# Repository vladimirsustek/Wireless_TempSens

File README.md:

<h2>The BleuPill tempSens!</h2>

<h2>Intended usages</h2>
<ol>
  <li>Battery operating low-power temperature sensor</li>
  <li>PID controlled loop (PWM H-Bridge)</li>
</ol>

System consist of: <br> 
<ol>
  <li>Core MCU - STM32F103C8T6 BluePill module</li>
  <li>nRF24L01+ wireless module</li>
  <li>LM75AD temperature sensor</li>
  <li>2x NTC 10k on-board sensor</li>
  <li>Optional PWM H-Bridge DRV8220</li>
  <li>Optional self-measuring current consumption circuit (OA LMV358 1/2 sensing 10Ohm) - curr</li>
  <li>Optional OA channel sensing general purpose external voltage (LMV358 2/2) - oagp</li>
</ol>

This project has default structure for STM's [STM32CudeIDE](https://www.st.com/en/development-tools/stm32cubeide.html#:~:text=STM32CubeIDE%20is%20an%20advanced%20C,and%20GDB%20for%20the%20debugging.)
.Download this free IDE to build the project.<br/>
**The project utilizes default STM's HAL drivers**<br/>

To see complete PCB design, see "PCB_design" directory, or at least the [schematic](/PCB_design/Wireless_TempSens.pdf)

<h2>Battery operating low-power temperature sensor</h2>

System shall periodically send all measured data in specified interval.<br/>
System shall consume minimal power when not measuring or sending the data .<br/>
System shall be parametrized over the UART (115200b, LF terminated):
<ol>
  <li>nRF24L01+'s TX_ADR: 5 - bytes e.g. ADR01</li>
  <li>nRF24L01+'s RX_ADR_P0: 5 - bytes e.g. ADR01</li>
  <li>PERIOD INTERVAL: number 0 - 255 representing low power mode in seconds</li>
</ol>
Note that the UART connection is meant as optional for parametrization and logging.

<h3>BluePill modifications</h3>
Due to the permanetly on PWR LED (when connected to the 3V3)<br/>
and the PC13 LED (on due to the TAMPER RTC-ALARM PIN),<br/>
their pull-up resistors has been desoldered (R5, R1).<br/>
Note that each LED consumed cca 2mA what is inadmissible for low power mode.

<h3>Startup and operational sequence<br/></h3>
After reset, the application sends UART messages:<br/><br/>
<em>LISTENING FOR PARAMETRIZATION 10000 ms<br/>
FORMAT: ADR01 ADR01 010</em><br/>...displaying currently set parameters<br/><br/>
When a new parameters has been received and set, they are displayed:<br/><br/>
<em>TX_ADR ADR01<br/>
RX_ADR ADR01<br/>
STOP_PERIOD 58<br/>
NORMAL MODE STARTED</em><br/>
When no or invalid parameters were provided:<br/><br/>
<em>NO CHANGES APPLIED<br/>
NORMAL MODE STARTED</em/>

Then, once per pre-set interval the system sends over the UART message:<br/><br/>
<em>TMPE 23750 - the temperature by the LM75AD [m°C]<br/>
NTC2 1334 - the NTC2 measured voltage [mV]<br/>
NTC1 1392  - the NTC1 measured voltage [mV]<br/>
NTC2 8998 - the NTC2 calculated resistance [mV]<br/> 
NTC1 9768 - the NTC1 calculated voltage [mV]<br/>
NTC2 274344 - the NTC2 interpolated temperature [m°C]<br/>
NTC1 255636 - the NTC1 interpolated temperature [m°C]<br/>
OAGP 1236 - the measured voltage on the oagp [mV]<br/>
CURR 1140 - the measured voltage on the curr [mV]<br/>
TMPI 34 - the MCU internal sensor temperature [°C]<br/>
VREF 2815 - the MCU power supply VDDA [mV]<br/>
NRF STATUS: 0x1e - the STATUS register of the nRF24L01</em><br/>

And also sends over the nRF24L01+ structure consist of (wireless):<br/><br/>
<em>int32_t ntc2;<br/>
int32_t ntc1;<br/>
int32_t oagp;<br/>
int32_t curr;<br/>
int32_t tmpi;<br/>
int32_t vdda;<br/>
int32_t tmpe;</em><br/>

With the same meaning like explained for the UART message.<br/>
The ntc2 and ntc1 is already the interpolated temperature value.<br/>

<h3>Low power current consumption</h3>

<h4>LP (Low Power) - STOP_MODE the deepest MCU sleep mode</h4>

According to the the [STM32F103C8T6 datasheet](/Docs/stm32f103cb.pdf) the STOP_MODE
consumption is 14uA for the VDDA = 3.3V<br>

As the BluePill utilizes the LDO [RT9193-33](/Docs/RT9193-33PB-Richtek.pdf) with
quescient current 90-130uA and all external peripherals are<br/>controlled using the
P-FET transistor with 470kOhm pull-up (7uA) - disconnected during the STOP_MODE.<br/>

The maximal STOP_MODE consumption for VDDA = 3.3V (5V BluePill power supply) is:<br/>

<em> I_LP = I_MCU_STOP_MODE + I_LDO_QUESCIENT + I_T_PULL_UP = 14uA + 130uA + 7uA = 150uA.

<h4>ON - measuring the temperatures/voltages</h4>

The On-Mode consumption mostly consist of the:<br/>

STM32CubeIDE:PCC_Tool_Calculator MCU consumption at 2MHz clock = 1.9mA<br/>
[LM75AD](/Docs/LM75A.pdf) normal mode consumption = 100uA<br/>
NTC1 + NTC2 consumption at 25°C (10k+10k) = 2x165uA = 330uA<br/>

<em> I_ON = I_MCU+ I_LM75AD + I_NTC = 1900uA + 100uA + 330uA = 2380uA</em>

<h4>TX - nRF24L01+ transmit with 16 repeat attempts, 4000us timeout</h4>

The TX mode:<br/>
nRF24L01+ consumption in TX mode (0dBm max power):

<em> I_TX = I_ON + I_NRF_TX  = 2380uA + 13000uA = 15080</em>

The maximal time spent in TX mode for payload = 32Bytes<br/>
bits_to_transmit = preamb + address + packet control field + payload + crc<br/>
bits_to_transmit = 8 + 5*8 + 9 + 32*8 + 2*8 = 329 bits<br/>

329bits are transmitted with 2Mbps in time 329/2,000,000 = 165us<br/>

However as the ACK mode is selected (the same amount might be sent back)<br/>
the duration 330us shall be taken in account (omitted other minor latencies).<br/>

To be sure, 16 re-transmits with 4000us timeout are selected.<br/>

thus I_TX might take up to cca 16x4000 = 64ms => 100ms TX time selected.<br/>

<br/>See the [nRF24L01+](nRF24L01Pluss_Preliminary_Product_Specification_v1_0.pdf) for more info<br/>

<h4>Average consumption</h4>

The average current consumption for the operational sequence:

I_ON = 1.9 seconds<br/>
I_TX = 0.1 seconds<br/>
I_LP = 58  seconds<br/>

I_AVG = (1.9x2380uA + 0.1x15080 + 58x150uA)/60 = 245uA<br/>

As the conventional AA or AAA batteries are providing good power down to the 0.9V,<br/>
and all the used components quarantie operation down to the 2.7V (3x0.9V)<br/>

For the 1500mAh batteries, expected durability of operation is:

t = 1500 / I_AVG = 1500 / 0.245 = 6122 hours => t = 255 days

<h4>Evaluation - Measured consumption</h4>

For the 5V power supply, I_LP = 116uA<br/>
For the 2.9V power supply, I_LP = 82uA<br/>

**Looks like the project fullfills the requirements !!**

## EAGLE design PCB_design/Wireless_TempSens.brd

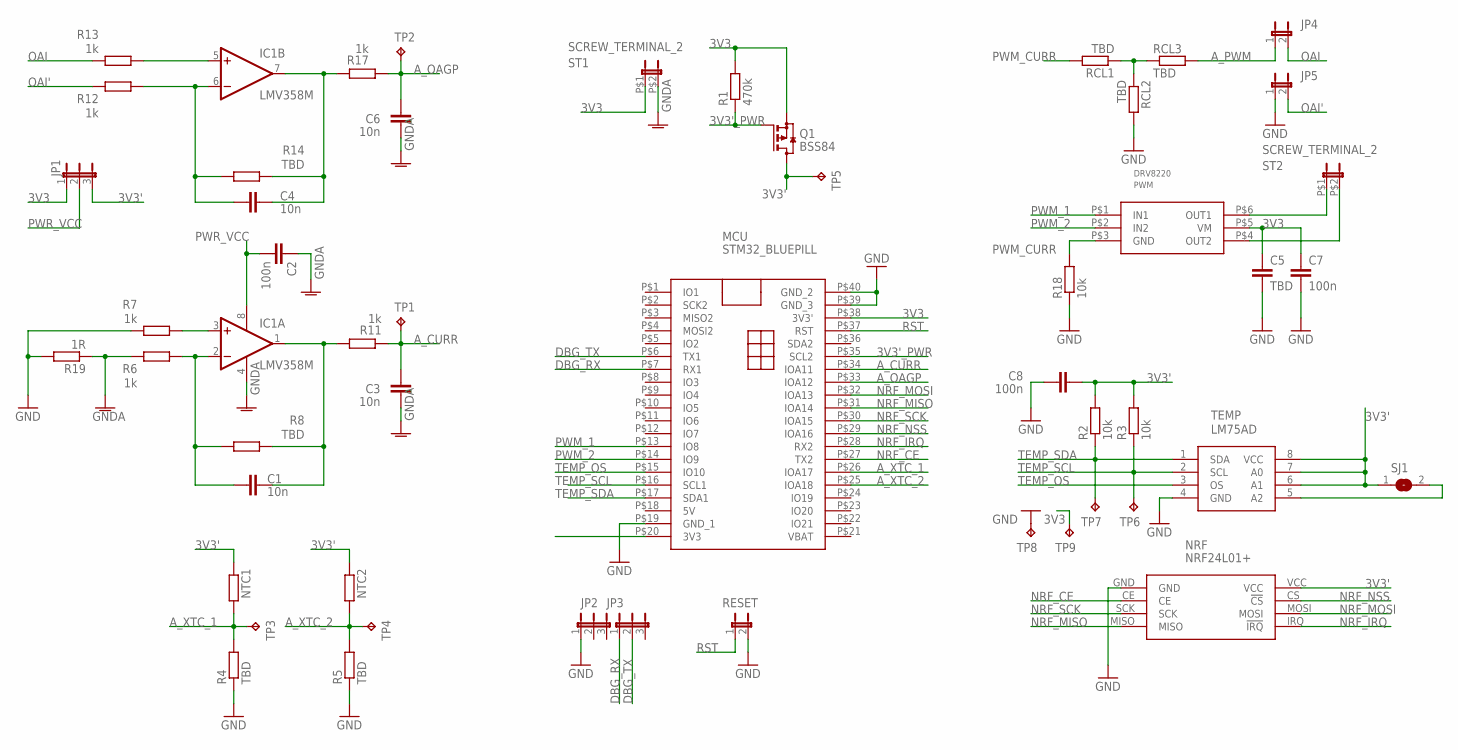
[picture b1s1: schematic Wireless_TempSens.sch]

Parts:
C1, C3, C4, C6: 10n; C0805
C2, C7, C8: 100n; C0805
C5: TBD; C0805
IC1: LMV358M; SO08
JP1, JP2, JP3: JP2E; JP2
JP4, JP5: JP1E; JP1
MCU: STM32_BLUEPILL
NRF: NRF24L01+
NTC1, NTC2: R-EU_0204/5; 0204/5
PWM: DRV8220; SOT-5X3
Q1: BSS84; SOT23
R1: 470k; R0805
R2, R3, R18: 10k; R0805
R4, R5, R8, R14: TBD; R0805
R6, R7, R11, R12, R13, R17: 1k; R0805
R19: 1R; R0805
RCL1, RCL2, RCL3: TBD; R0805
RESET: JP1E; JP1
SJ1: SJ
ST1, ST2: SCREW_TERMINAL_2; SCREW_TERMIANL_2
TEMP: LM75AD; SOIC8
TP1, TP2, TP3, TP4, TP5, TP6, TP7, TP8, TP9: TPPAD1-13; P1-13

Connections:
3V3: C5.1, C7.1, JP1.1, MCU.P$20 (3V3), MCU.P$38 (3V3'), PWM.P$5 (VM), Q1.2 (S), R1.2, ST1.P$1 (1), TP9.TP
3V3': C8.2, JP1.3, NRF.VCC, NTC1.1, NTC2.1, Q1.3 (D), R2.2, R3.2, SJ1.1, TEMP.6 (A1), TEMP.7 (A0), TEMP.8 (VCC), TP5.TP
3V3'_PWR: MCU.P$35 (SCL2), Q1.1 (G), R1.1
A_CURR: C3.2, MCU.P$34 (IOA11), R11.1, TP1.TP
A_OAGP: C6.2, MCU.P$33 (IOA12), R17.1, TP2.TP
A_PWM: JP4.1, RCL3.2
A_XTC_1: MCU.P$26 (IOA17), NTC1.2, R4.2, TP3.TP
A_XTC_2: MCU.P$25 (IOA18), NTC2.2, R5.2, TP4.TP
DBG_RX: JP3.1, MCU.P$7 (RX1)
DBG_TX: JP3.2, MCU.P$6 (TX1)
GND: C5.2, C7.2, C8.1, JP2.1, JP5.1, MCU.P$19 (GND_1), MCU.P$39 (GND_3), MCU.P$40 (GND_2), NRF.GND, R4.1, R5.1, R7.2, R18.1, R19.2, RCL2.2, RESET.2, TEMP.4 (GND), TP8.TP
GNDA: C2.1, C3.1, C6.1, IC1.4 (V-), R6.2, R19.1, ST1.P$2 (2)
unnamed: IC1.3 (+IN), R7.1
unnamed: C1.2, IC1.2 (-IN), R6.1, R8.2
unnamed: C1.1, IC1.1 (OUT), R8.1, R11.2
unnamed: IC1.5 (+IN), R13.1
unnamed: C4.2, IC1.6 (-IN), R12.1, R14.2
unnamed: C4.1, IC1.7 (OUT), R14.1, R17.2
unnamed: SJ1.2, TEMP.5 (A2)
unnamed: PWM.P$6 (OUT1), ST2.P$1 (1)
unnamed: PWM.P$4 (OUT2), ST2.P$2 (2)
unnamed: RCL1.1, RCL2.1, RCL3.1
NRF_CE: MCU.P$27 (TX2), NRF.CE
NRF_IRQ: MCU.P$28 (RX2), NRF.IRQ (!IRQ)
NRF_MISO: MCU.P$31 (IOA14), NRF.MISO
NRF_MOSI: MCU.P$32 (IOA13), NRF.MOSI
NRF_NSS: MCU.P$29 (IOA16), NRF.CS (!CS)
NRF_SCK: MCU.P$30 (IOA15), NRF.SCK
OAI: JP4.2, R13.2
OAI': JP5.2, R12.2
PWM_1: MCU.P$13 (IO8), PWM.P$1 (IN1)
PWM_2: MCU.P$14 (IO9), PWM.P$2 (IN2)
PWM_CURR: PWM.P$3 (GND), R18.2, RCL1.2
PWR_VCC: C2.2, IC1.8 (V+), JP1.2
RST: MCU.P$37 (RST), RESET.1
TEMP_OS: MCU.P$15 (IO10), TEMP.3 (OS)
TEMP_SCL: MCU.P$16 (SCL1), R3.1, TEMP.2 (SCL), TP6.TP
TEMP_SDA: MCU.P$17 (SDA1), R2.1, TEMP.1 (SDA), TP7.TP

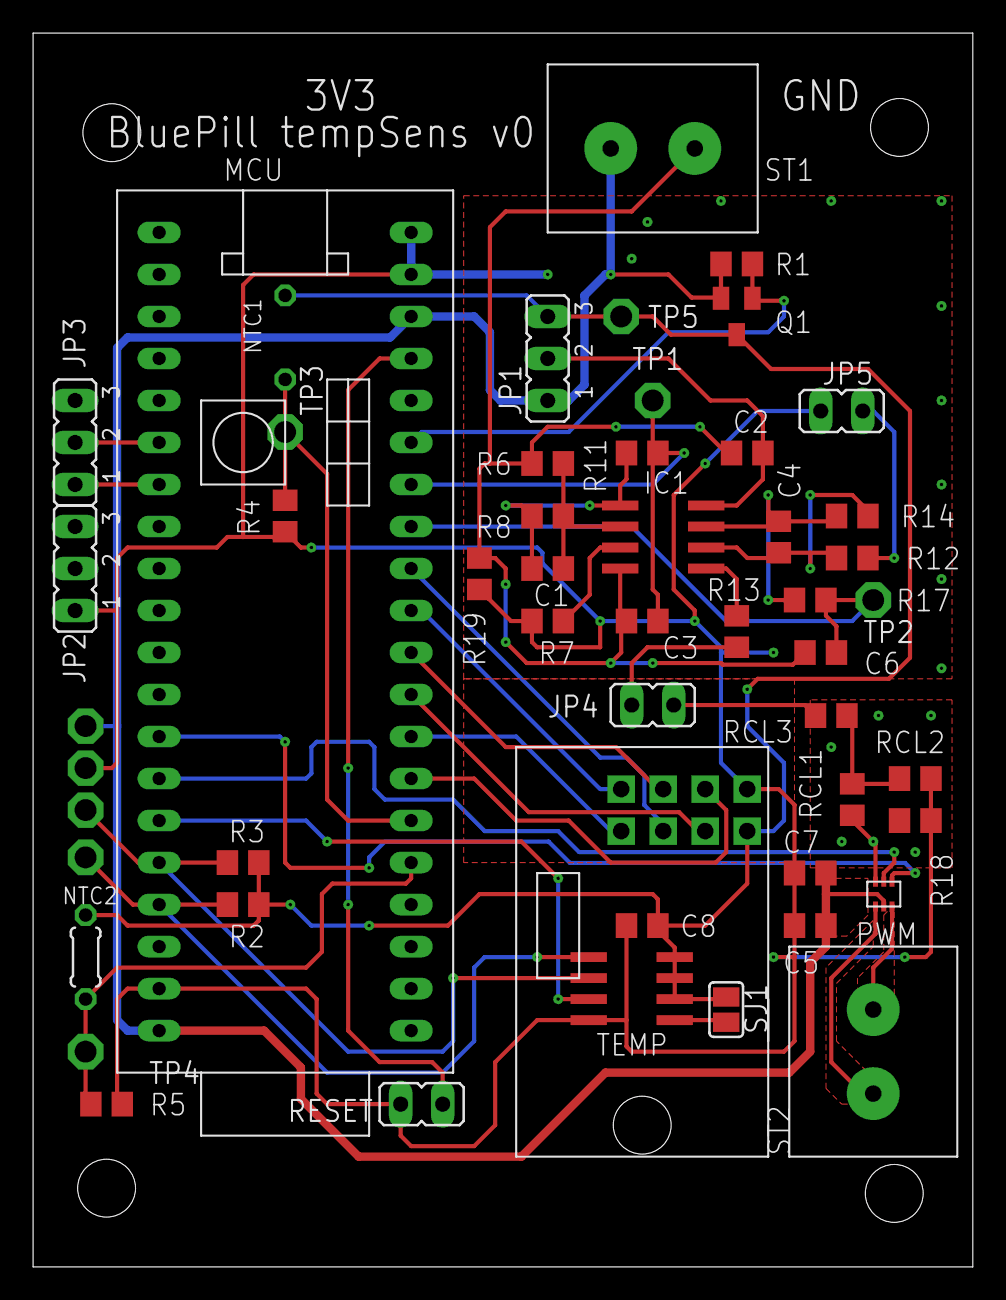
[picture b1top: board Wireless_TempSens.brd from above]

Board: 2 copper layers, 56.8 x 74.6 mm, 52 parts (1 on the bottom side), 38 nets.

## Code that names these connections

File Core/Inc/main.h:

/* USER CODE BEGIN Header */
/**
  ******************************************************************************
  * @file           : main.h
  * @brief          : Header for main.c file.
  *                   This file contains the common defines of the application.
  ******************************************************************************
  * @attention
  *
  * Copyright (c) 2023 STMicroelectronics.
  * All rights reserved.
  *
  * This software is licensed under terms that can be found in the LICENSE file
  * in the root directory of this software component.
  * If no LICENSE file comes with this software, it is provided AS-IS.
  *
  ******************************************************************************
  */
/* USER CODE END Header */

/* Define to prevent recursive inclusion -------------------------------------*/
#ifndef __MAIN_H
#define __MAIN_H

#ifdef __cplusplus
extern "C" {
#endif

/* Includes ------------------------------------------------------------------*/
#include "stm32f1xx_hal.h"

/* Private includes ----------------------------------------------------------*/
/* USER CODE BEGIN Includes */

/* USER CODE END Includes */

/* Exported types ------------------------------------------------------------*/
/* USER CODE BEGIN ET */

/* USER CODE END ET */

/* Exported constants --------------------------------------------------------*/
/* USER CODE BEGIN EC */

/* USER CODE END EC */

/* Exported macro ------------------------------------------------------------*/
/* USER CODE BEGIN EM */

/* USER CODE END EM */

/* Exported functions prototypes ---------------------------------------------*/
void Error_Handler(void);

/* USER CODE BEGIN EFP */

/* USER CODE END EFP */

/* Private defines -----------------------------------------------------------*/
#define NTC_2_Pin GPIO_PIN_0
#define NTC_2_GPIO_Port GPIOA
#define NTC_1_Pin GPIO_PIN_1
#define NTC_1_GPIO_Port GPIOA
#define NRF_CE_Pin GPIO_PIN_2
#define NRF_CE_GPIO_Port GPIOA
#define NRF_IRQ_Pin GPIO_PIN_3
#define NRF_IRQ_GPIO_Port GPIOA
#define NRF_NCS_Pin GPIO_PIN_4
#define NRF_NCS_GPIO_Port GPIOA
#define NRF_SCK_Pin GPIO_PIN_5
#define NRF_SCK_GPIO_Port GPIOA
#define NRF_MISO_Pin GPIO_PIN_6
#define NRF_MISO_GPIO_Port GPIOA
#define NRF_MOSI_Pin GPIO_PIN_7
#define NRF_MOSI_GPIO_Port GPIOA
#define OAGP_Pin GPIO_PIN_0
#define OAGP_GPIO_Port GPIOB
#define CURR_Pin GPIO_PIN_1
#define CURR_GPIO_Port GPIOB
#define PWR_3V3_Pin GPIO_PIN_10
#define PWR_3V3_GPIO_Port GPIOB
#define TEMP_OS_Pin GPIO_PIN_7
#define TEMP_OS_GPIO_Port GPIOB
#define TEMP_SCL_Pin GPIO_PIN_8
#define TEMP_SCL_GPIO_Port GPIOB
#define TEMP_SDA_Pin GPIO_PIN_9
#define TEMP_SDA_GPIO_Port GPIOB

/* USER CODE BEGIN Private defines */

/* USER CODE END Private defines */

#ifdef __cplusplus
}
#endif

#endif /* __MAIN_H */

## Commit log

2023-03-06 Updated documentation
2023-03-10 Functional NRF24L01+, ADC internal measurements
2023-03-11 Operational sensor ready for server debug
2023-03-12 Added DEBUG_PRINT, fixed paths, observing ADC indexing offset
2023-03-12 Release prepared
2023-03-12 Minor path fixes
2023-04-24 Porting to the BluePill tempSens v0, int ADC ok, LM75AD ok
2023-04-27 Complete "SLEEPmode" solution before cleanup
2023-04-27 "SLEEPmode" Cleanup
2023-04-27 Added minus temperatures for LM75AD
2023-05-07 DEBUG release, 130uA STOP mode, 58s period
2023-05-09 Supported NVM command "ADR01 ADR01 058" (TX_RXP0_STOP_MODE)
2023-05-11 Rotated picture
2023-05-11 Minor format changes
2023-05-11 Corrected readme link
2023-05-12 Bugfixing (I2C stable, corrected internal temperature)
